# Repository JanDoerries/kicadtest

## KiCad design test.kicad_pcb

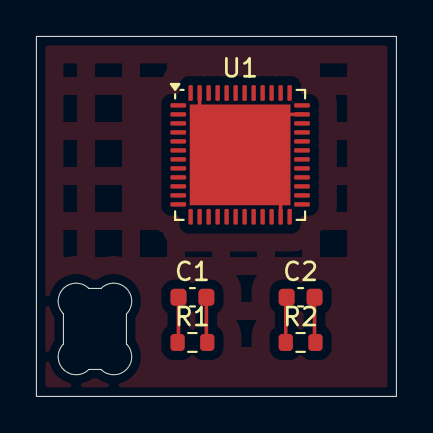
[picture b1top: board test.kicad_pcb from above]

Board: 2 copper layers, 20.0 x 20.0 mm, 5 parts (0 on the bottom side), 5 nets.

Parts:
C1, C2: C; C_0603_1608Metric
R1, R2: R; R_0603_1608Metric
U1: STM32F401C_D-E_Ux; QFN-48-1EP_7x7mm_P0.5mm_EP5.6x5.6mm

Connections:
unnamed: C1.1, R1.1
unnamed: C1.2, R1.2
unnamed: C2.1, R2.1
unnamed: C2.2, R2.2
unnamed: U1.23 (VSS), U1.35 (VSS), U1.47 (VSS), U1.49 (VSS)

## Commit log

2025-02-20 init
2025-02-20 added OSC
2025-02-20 added traces
2025-02-20 back side
2025-02-20 commit project
2025-02-20 Added cool text
2025-02-20 removed connection
2025-02-20 added connection
